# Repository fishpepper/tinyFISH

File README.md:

# tinyFISH -- tiny / light / f3 / integrated receiver

My approach to build a small and lightweight flight controller.

See [http://fishpepper.de/projects/tinyFISH](http://fishpepper.de/projects/tinyFISH) for more details.

This thing is TINY! The outer dimensions are 20x20mm with a 16mm hole-to-hole spacing.
It runs betaflight and includes a FrSky compatible RX, a current- and
voltage-sensor, a blackbox logger, and it is open hardware -- go and build one yourself!

Key features:
- STM32F303 CPU
- MPU6000 gyro (SPI connection!)
- integrated FrSky compatible rx based on [uSKY](http://fishpepper.de/projects/uSKY)
- integrated current- and voltage sensor
- integrated blackbox logger
- betaflight ready

This work is published under the CERN open hardware license v1.2. 
Feel free to use the design - but make sure to give proper credit 
and release all modifications under the same license! 
See LICENSE.txt for details!

THIS COMES WITH NO WARRANTY! BUILD, FLY, AND USE AT YOUR OWN RISK!

# Build your own

Make sure to init the git submodule for the libraries in the
kicad_misc directory by calling git submodule init && git submodule update.
You will have to use a recent kicad version, i used the commit #efdfaeb
when i designed this circuit board. Older versions will probably not work.

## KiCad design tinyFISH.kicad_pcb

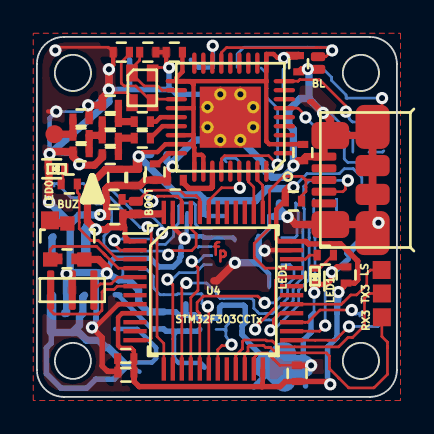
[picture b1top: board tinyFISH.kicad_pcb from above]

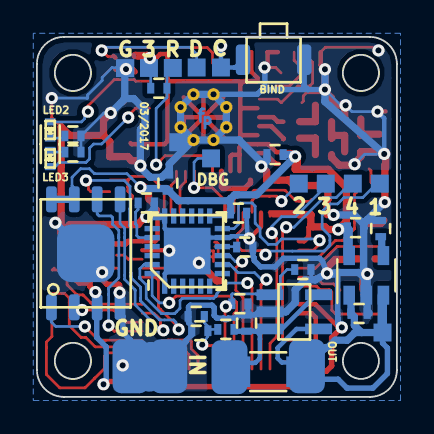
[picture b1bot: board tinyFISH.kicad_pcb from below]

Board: 2 copper layers, 20.0 x 20.0 mm, 87 parts (40 on the bottom side), 56 nets.

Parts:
ANT1: TP; smd_1x1_round
BIND1: CUSTOM_PUSHBUTTON; OMRON_B3U-3000P
BL1: BL; SOLDERBRIDGE
C1, C10, C17, C23: 1u; C_0402_CUSTOM
C2, C6: 12p; C_0402_CUSTOM
C3, C13, C14, C16, C19, C20, C21, C22, C25, C26, C27, C29: 100n; C_0402_CUSTOM
C4, C7: 100p; C_0402_CUSTOM
C5: 220p; C_0402_CUSTOM
C8, C9: 1p; C_0402_CUSTOM
C11: 1p8; C_0402_CUSTOM
C12: 1p5; C_0402_CUSTOM
C15: 2n2; C_0402_CUSTOM
C18: 4u7; C_0402_CUSTOM
C24, C30: 10n; C_0402_CUSTOM
C28: NC; C_0402_CUSTOM
DEBUG1: TP; TP_1x1
GND_IN1: GND; PAD_2x3
GND_MOUNT_2: GND; TP_1x1
GND_OUT1: GND; PAD_2x3
H1, H2, H3, H4: hole; mouting_hole
ISP_3V1: TP; TP_1x1
ISP_CLOCK1: TP; TP_1x1
ISP_DATA1: TP; TP_1x1
ISP_GND1: TP; TP_1x1
JP0: BOOT0; SOLDERBRIDGE
L1, L2, L3: 1.2nH; L_0402_CUSTOM
LED0: BLUE; LED_0402
LED1, LED3: RED; LED_0402
LED2: GREEN; LED_0402
Q1: SI2302DS; SI2302DS_SOT-23
R1, R5, R10: 10k; R_0402_CUSTOM
R3: 56k; R_0402_CUSTOM
R4: 220; R_0402_CUSTOM
R6, R8: 330; R_0402_CUSTOM
R7: 100; R_0402_CUSTOM
R9: 1k5; R_0402_CUSTOM
R11, R501: 1k; R_0402_CUSTOM
R12: 0R005; R_1206
R13: 30k; R_0402_CUSTOM
TP_1: WS2812; TP_1x1
TP_2: UART3_RX; TP_1x1
TP_3: UART3_RX1; TP_1x1
TP_4: BUZZER_GND; TP_1x1
TP_5: BUZZER_VCC; TP_1x1
TP_ESC_0: ESC_0; TP_1x1
TP_ESC_1: ESC_1; TP_1x1
TP_ESC_2: ESC_2; TP_1x1
TP_ESC_3: ESC_3; TP_1x1
U1: CC2510; QFN36_CC2510
U2: MPU-6000; QFN-24
U3: LP2985AIM5-3.0/NOPB; SOT-23-5
U4: STM32F303CCTx; LQFP-48_7x7mm_Pitch0.5mm
U5: M25P16-VME; VFDFPN8
U6: MICRO_USB_B; USB_MICRO_MOLEX
U7: INA139; DBV
VBAT1: CONN_1; PAD_2x3
VBAT_IN1: CONN_1; PAD_2x3
X1: 26MHz; crystal_2016
X2: 8MHz; CSTCE_G_A

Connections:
3V: C3.1, C5.1, C10.1, C13.1, C16.2, C18.1, C19.1, C20.1, C21.1, C22.1, C23.1, C24.1, C25.1, C29.1, ISP_3V1.1, JP0.1, R5.1, R9.1, U1.2, U1.10, U1.19, U1.22, U1.25, U1.26, U1.28, U1.29, U2.13, U3.5, U4.1, U4.9, U4.24, U4.36, U4.48, U5.3, U5.7, U5.8
/power/BAT+: C26.2, R10.2, R12.1, U7.3, U7.5, VBAT_IN1.1
/rx/ANT_N: C4.1, U1.24
/rx/ANT_P: C7.1, U1.23
/rx/ISP_CLOCK: BIND1.1, ISP_CLOCK1.1, U1.16
/rx/ISP_DATA: BL1.1, ISP_DATA1.1, U1.15
/rx/~RESET: R5.2, U1.31
ADC_CURRENT: C28.2, R13.1, U4.18, U7.1
ADC_VBAT: C27.1, R10.1, R11.2, U4.19
BUZZER: Q1.D, TP_4.1
BUZZER_IO: Q1.G, R501.2, U4.4
ESC_0: TP_ESC_0.1, U4.45
ESC_1: TP_ESC_1.1, U4.46
ESC_2: TP_ESC_2.1, U4.13
ESC_3: TP_ESC_3.1, U4.12
FLASH_CS: U4.25, U5.1
FLASH_MISO: U4.27, U5.2
FLASH_MOSI: U4.28, U5.5
FLASH_SCK: U4.26, U5.6
GND: BIND1.2, BL1.2, C1.1, C2.2, C3.2, C5.2, C6.2, C8.1, C10.2, C11.1, C12.1, C13.2, C14.2, C15.1, C16.1, C17.2, C18.2, C19.2, C20.2, C21.2, C22.2, C23.2, C24.2, C25.2, C26.1, C27.2, C28.1, C29.2, C30.2, GND_IN1.1, GND_MOUNT_2.1, GND_OUT1.1, ISP_GND1.1, L1.1, LED0.1, LED1.1, Q1.S, R1.2, R3.1, R4.2, R6.2, R11.1, R13.2, R501.1, U1.GND, U2.1, U2.11, U2.18, U3.2, U4.8, U4.23, U4.35, U4.47, U5.4, U6.5, U7.2, X1.2, X1.4, X2.2
LED_0: R7.1, U4.3
LED_1: R8.1, U4.34
MPU_EXTI: U2.12, U4.2
MPU_SPI_CS: U2.8, U4.14
MPU_SPI_MISO: U2.9, U4.16
MPU_SPI_MOSI: U2.24, U4.17
MPU_SPI_SCK: U2.23, U4.15
unnamed: ANT1.1, C12.2, L3.2
unnamed: C1.2, U1.30
unnamed: C2.1, U1.20, X1.1
unnamed: C4.2, C9.1, L1.2
unnamed: C6.1, U1.21, X1.3
unnamed: C7.2, C8.2, L2.1
unnamed: C9.2, C11.2, L2.2, L3.1
unnamed: C14.1, U2.10
unnamed: C15.2, U2.20
unnamed: C30.1, U3.4
unnamed: JP0.2, R1.1, U4.44
unnamed: LED0.2, R7.2
unnamed: LED1.2, R8.2
unnamed: LED2.1, R4.1
unnamed: LED2.2, U1.9
unnamed: LED3.1, R6.1
unnamed: LED3.2, U1.6
unnamed: R3.2, U1.27
unnamed: R9.2, U4.33, U6.3
unnamed: U4.5, X2.1
unnamed: U4.6, X2.3
unnamed: U4.32, U6.2
RX_DEBUG: DEBUG1.1, U1.33, U4.43
RX_HUB_TELEMETRY: U1.35, U4.37
RX_SBUS: U1.34, U4.38
UART3_RX: TP_3.1, U4.22
UART3_TX: TP_2.1, U4.21
VBAT: C17.1, R12.2, TP_5.1, U3.1, U3.3, U7.4, VBAT1.1
WS2812: TP_1.1, U4.29

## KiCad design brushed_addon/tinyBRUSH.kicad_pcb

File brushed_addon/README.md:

brushless_addon for tinyFISH FC -- convert your tinyFISH fc to brushed

this tiny add-on board will convert the tinyFISH fc into a brushed FC

this is open hardware - see LICENSE for details

THIS COMES WITH NO WARRANTY! BUILD AND USE AT YOUR OWN RISK!

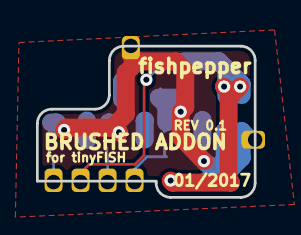
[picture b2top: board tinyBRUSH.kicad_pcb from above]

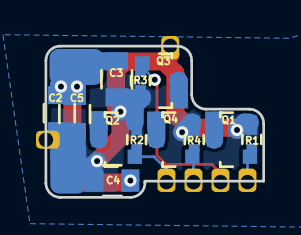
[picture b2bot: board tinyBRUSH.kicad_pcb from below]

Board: 2 copper layers, 12.1 x 8.4 mm, 24 parts (18 on the bottom side), 10 nets.

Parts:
C2, C3, C4, C5: 47u; C_0805
Q1, Q2, Q3, Q4: FET_N; SI2302DS_SOT-23
R1, R2, R3, R4: 10k; R_0402
TP1: ESC_0; edge_conn_1mm
TP2: ESC_1; edge_conn_1mm
TP3: ESC_2; edge_conn_1mm
TP4: ESC_3; edge_conn_1mm
TP5: M-_0; TP_1x1
TP6: M-_1; TP_1x1
TP7: M-_2; TP_1x1
TP8: M-_3; TP_1x1
TP9: VBAT; PAD_2x3
TP10: GND; PAD_2x3
TP11, TP12: GND; edge_conn_1mm

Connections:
GND: C2.2, C3.2, C4.2, C5.2, Q1.S, Q2.S, Q3.S, Q4.S, R1.2, R2.2, R3.2, R4.2, TP10.1, TP11.1, TP12.1
unnamed: C2.1, C3.1, C4.1, C5.1, TP9.1
unnamed: Q1.D, TP5.1
unnamed: Q1.G, R1.1, TP1.1
unnamed: Q2.D, TP6.1
unnamed: Q2.G, R2.1, TP2.1
unnamed: Q3.D, TP7.1
unnamed: Q3.G, R3.1, TP3.1
unnamed: Q4.D, TP8.1
unnamed: Q4.G, R4.1, TP4.1

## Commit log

2016-12-29 initial release
2016-12-30 fixed datestamp
2017-01-02 adding doc
2017-01-02 fixed +-
2017-01-10 added bind button
2017-01-10 rev 02 oshpark job
2017-01-10 updated doc
2017-01-13 some cosmetic cleanup, fixed esc4 naming
2017-01-13 added omron switch to lib
2017-01-13 added brushed addon board
2017-01-15 swapped blue and red led
2017-01-16 cleanup and added 3d shapes
2017-01-16 adding automatic gfx generation
2017-01-18 new generator script
2017-02-05 added border
2017-02-21 cleanup to custom r and c parts
2017-03-21 fixed rev id
2017-03-21 fixed naming of pads
2017-03-21 fixed vreg
2017-03-21 fixed doc
2017-03-21 fixed doc for esc
